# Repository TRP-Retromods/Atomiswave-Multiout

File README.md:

# Atomiswave Multiout
---
Get Composite, RGB or S-Video output from your Atomiswave, using the VGA output

(c) 2023 by The Real Phoenix
Design from Mike Chi's VGA2SCART

---

## Features:
- The motherboard is doing all the job, the "hat" or daughterboard is the one with the output connectors, so you can make one for your needs
- PAL/NTSC selection
- LP Filter
- Audio Line-in level is driven from the daughterboard, leaving the ability to keep pass-trought audio for amp already present inside a cabinet

## Notes:
- You'll need to program the CDCE either with using a DFO programmer or ask your ICs provider to do it for you.
- The connector to audio/power is tricky to find, I found some on eBay: https://www.ebay.ca/itm/184681041924

---
### Links for the Programmer and classic DFO:
https://nfggames.com/forum2/index.php?topic=5744.0
https://oshpark.com/profiles/micro

https://circuit-board.de/forum/index.php/Thread/7810-Sega-32X-Switchless-Mod-f%C3%BCr-Mega-Drive-1-und-auch-2/?s=005d89b5fd35d5ff06d198493b633b89d1ca043f

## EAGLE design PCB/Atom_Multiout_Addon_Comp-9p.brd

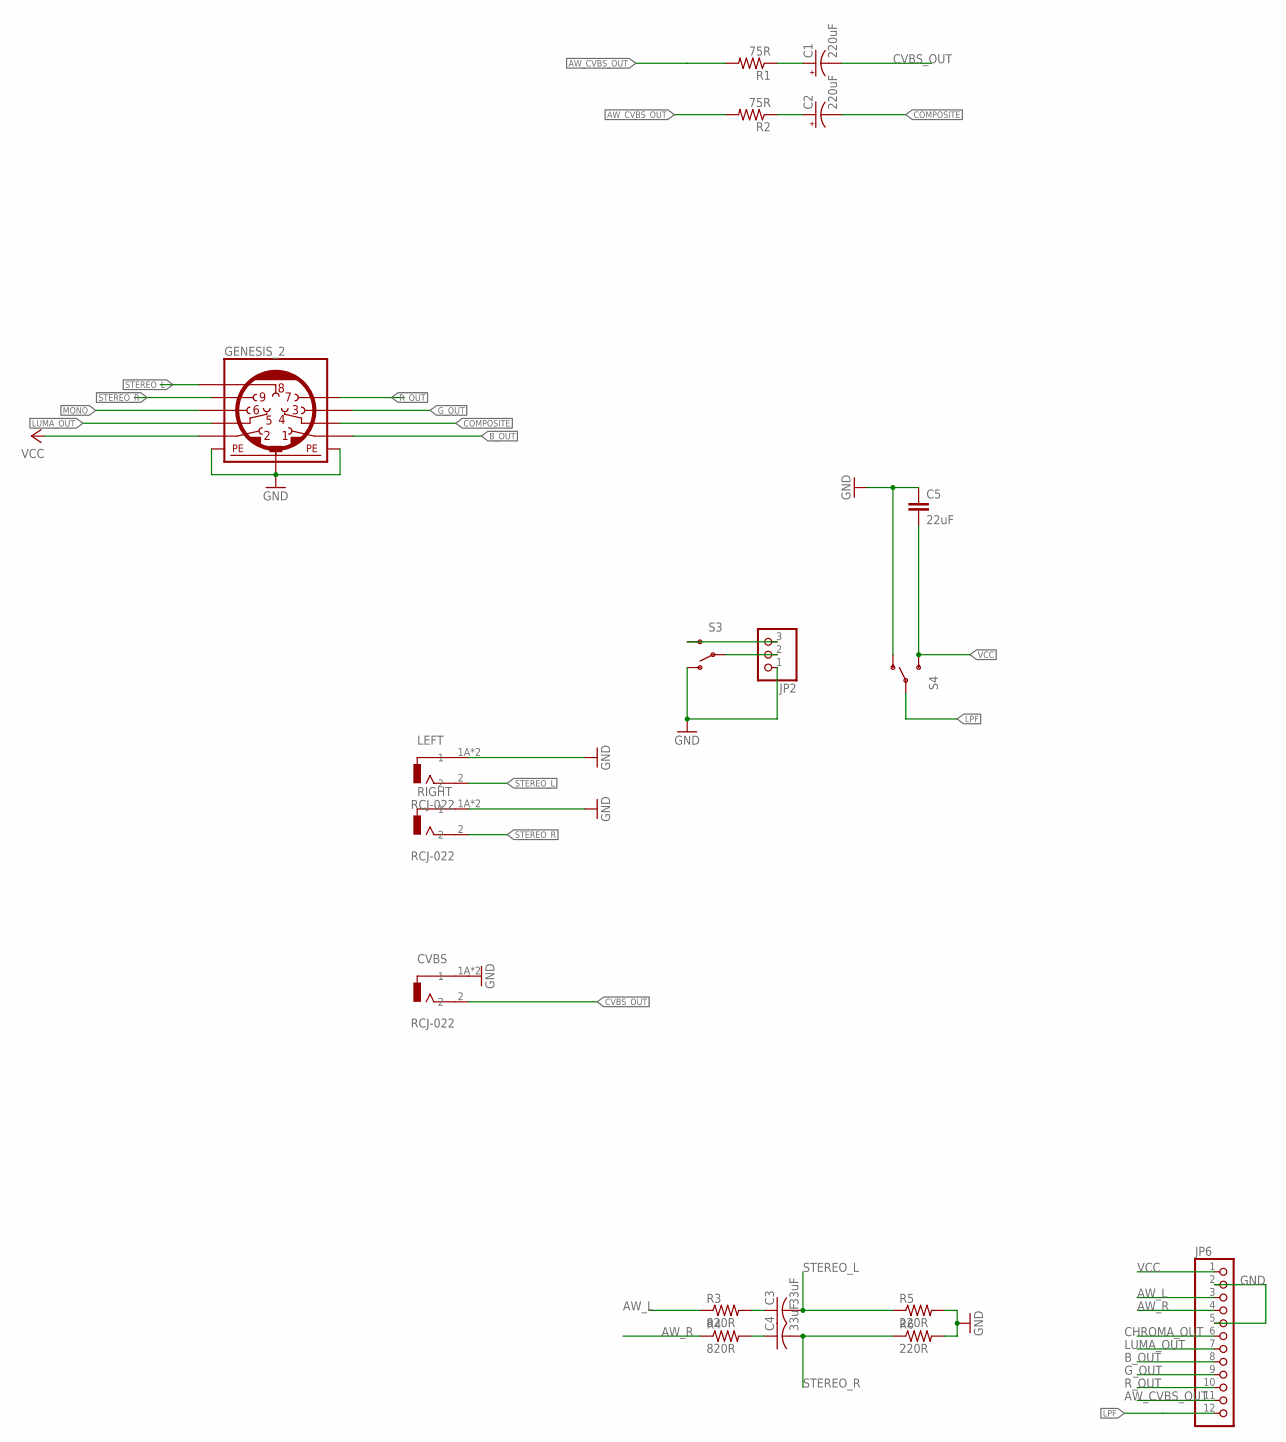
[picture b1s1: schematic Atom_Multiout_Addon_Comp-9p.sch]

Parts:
C1, C2: 220uF; D/7343-31W
C3, C4: 33uF; C1206K
C5: 22uF; C0603
CVBS: RCJ-022; CUI_RCJ-022
GENESIS_2: MINI_DIN_9; M_DIN9
JP2: PINHD-1X03_2.54-S; 1X03-S
JP6: PINHD-1X12_2.54-S; 1X12-S
LEFT: RCJ-022; CUI_RCJ-022
R1, R2: 75R; R1206
R3, R4: 820R; R1206
R5, R6: 220R; R1206
RIGHT: RCJ-022; CUI_RCJ-022
S3, S4: SWITCH-SPDT-SMD-A; SWITCH-SPST-SMD-A

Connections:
AW_CVBS_OUT: JP6.11, R1.2, R2.2
AW_L: JP6.3, R3.1
AW_R: JP6.4, R4.1
B_OUT: GENESIS_2.1, JP6.8
CHROMA_OUT: JP6.6
COMPOSITE: C2.-, GENESIS_2.4
CVBS_OUT: C1.-, CVBS.2
GND: C5.1, CVBS.1A (1), CVBS.1B (1), GENESIS_2.SH1 (PE1), GENESIS_2.SH2 (PE2), GENESIS_2.SH3 (PE3), JP2.1, JP6.2, JP6.5, LEFT.1A (1), LEFT.1B (1), R5.2, R6.2, RIGHT.1A (1), RIGHT.1B (1), S3.1 (O), S4.1 (O)
G_OUT: GENESIS_2.3, JP6.9
LPF: JP6.12, S4.2
LUMA_OUT: GENESIS_2.5, JP6.7
MONO: GENESIS_2.6
unnamed: C2.+, R2.1
unnamed: JP2.3, S3.3 (S)
unnamed: C1.+, R1.1
unnamed: C4.1, R4.2
unnamed: C3.1, R3.2
unnamed: JP2.2, S3.2
R_OUT: GENESIS_2.7, JP6.10
STEREO_L: C3.2, GENESIS_2.8, LEFT.2, R5.1
STEREO_R: C4.2, GENESIS_2.9, R6.1, RIGHT.2
VCC: C5.2, GENESIS_2.2, JP6.1, S4.3 (S)

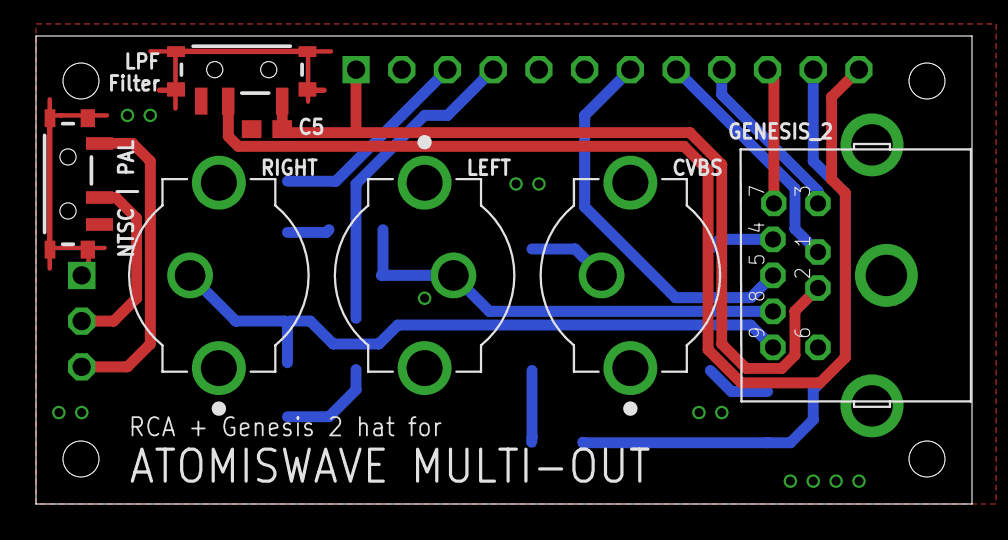
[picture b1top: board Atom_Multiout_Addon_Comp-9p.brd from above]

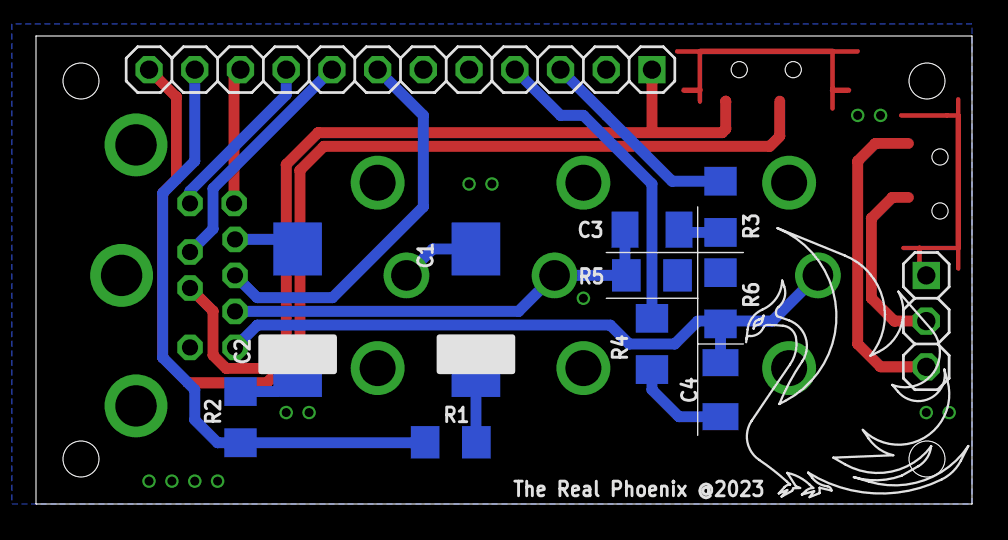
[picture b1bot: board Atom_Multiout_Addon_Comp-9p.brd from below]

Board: 2 copper layers, 52.0 x 26.0 mm, 20 parts (13 on the bottom side), 20 nets.

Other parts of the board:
U$1: LOGO

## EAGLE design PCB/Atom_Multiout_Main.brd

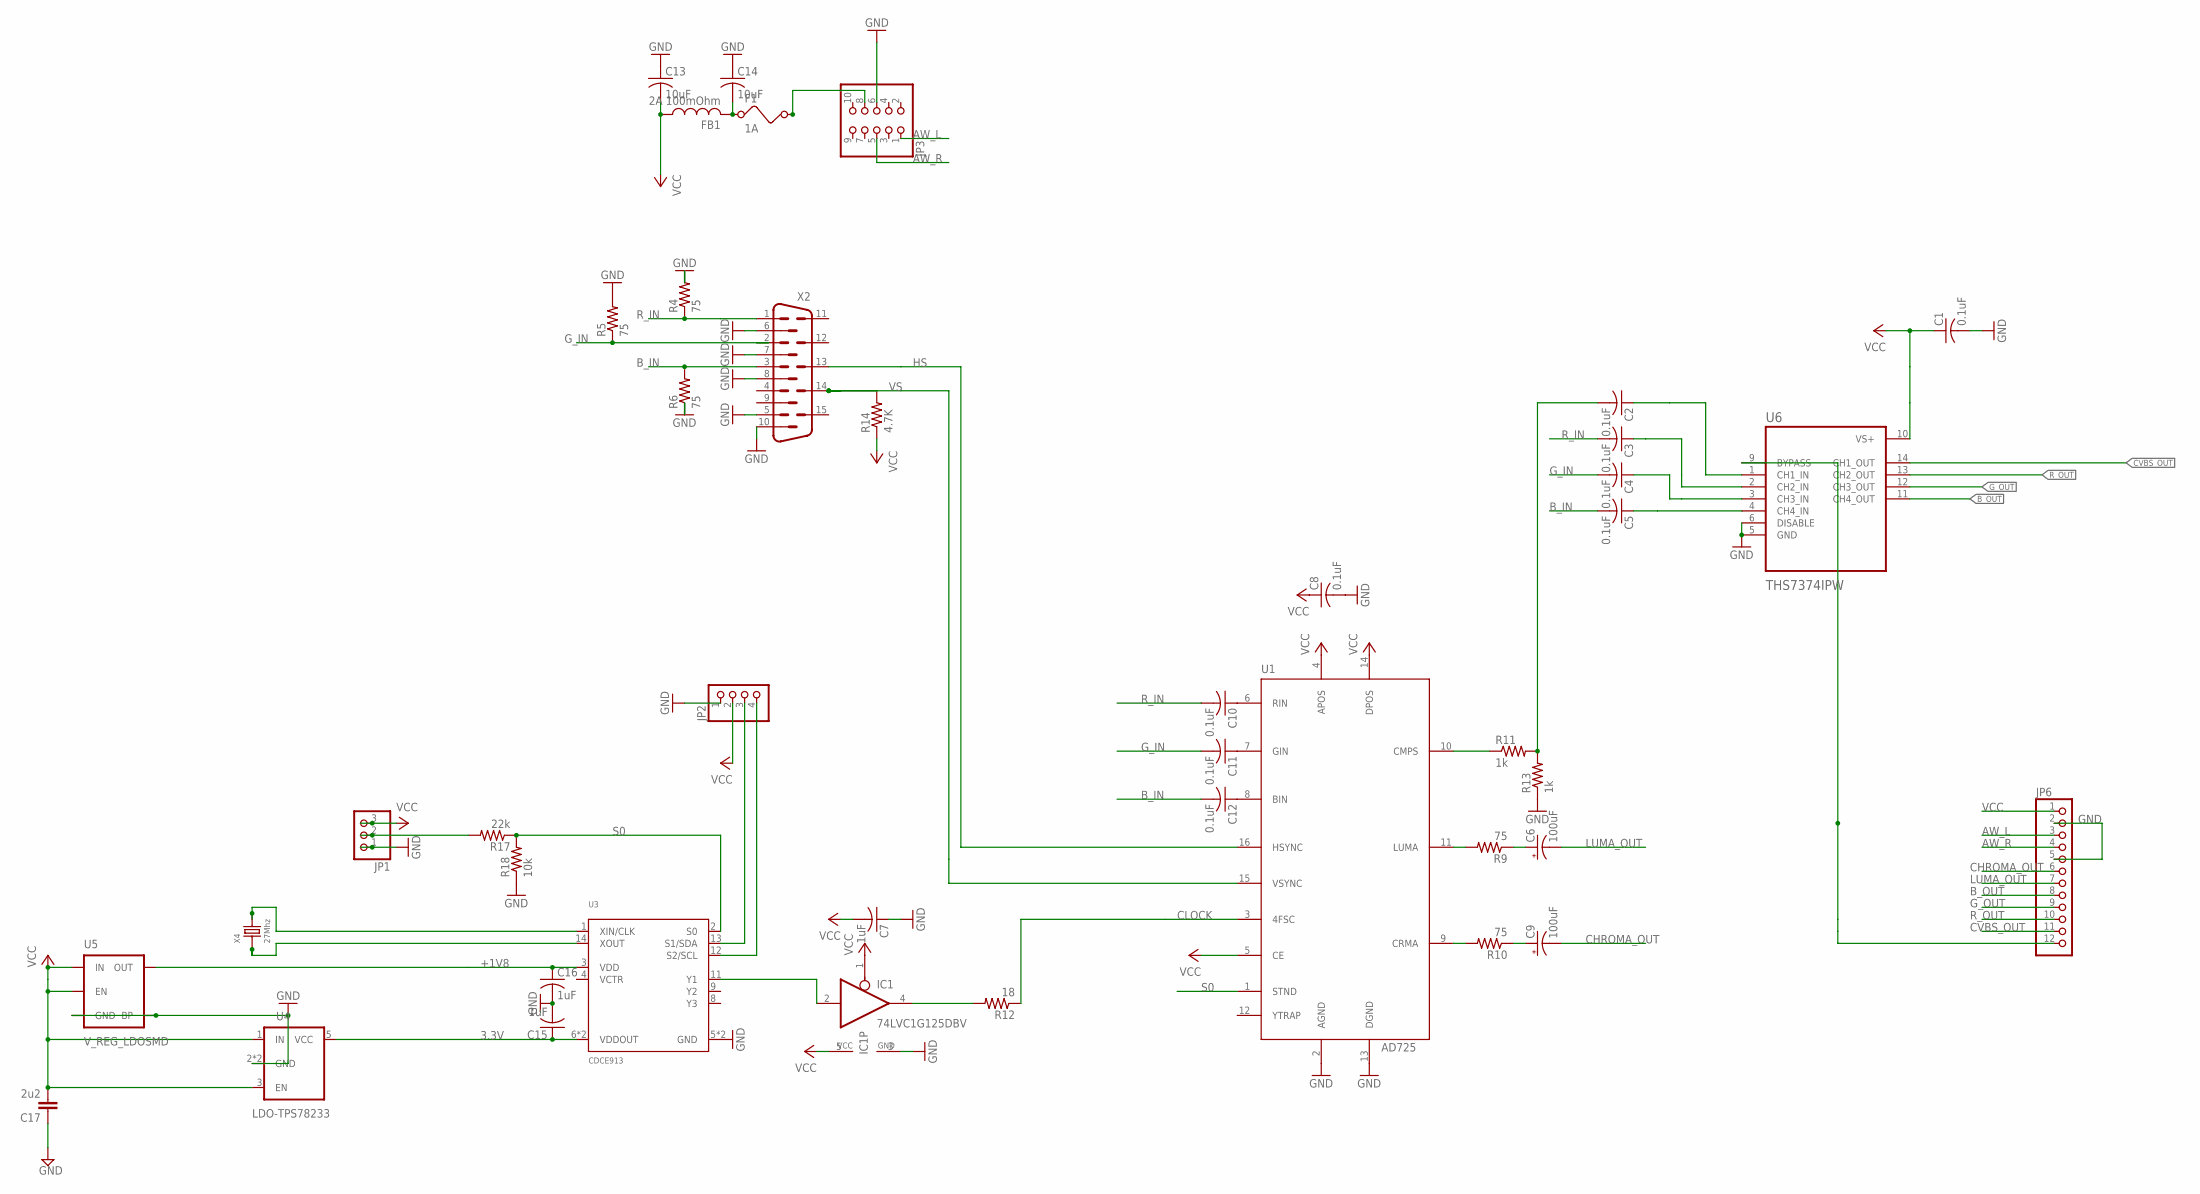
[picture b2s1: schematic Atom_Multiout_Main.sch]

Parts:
C1, C2, C3, C4, C5, C8, C10, C11, C12: 0.1uF; C0603@1
C6, C9: 100uF; C/6032-28R
C7, C15, C16: 1uF; C0603@1
C13, C14: 10uF; C0603@1
C17: 2u2; C0603
F1: 1A; 1812
FB1: 2A 100mOhm; 0805
IC1: 74LVC1G125DBV; SOT23-5
JP1: PINHD-1X03_2.54-S; 1X03-S
JP2: PINHD-1X04_2.00; 1X04M
JP3: PINHD-2X05_2.00; 2X05M
JP6: PINHD-1X12_2.54-S; 1X12-S
R4, R5, R6, R9, R10: 75; R0603
R11, R13: 1k; R0603
R12: 18; R0603
R14: 4.7K; R0603
R17: 22k; R0603
R18: 10k; R0603
U1: AD725; SOIC16W
U3: CDCE913; TSSOP14
U4: LDO-TPS78233; SOT23-5
U5: V_REG_LDOSMD; SOT23-5
U6: THS7374IPW; SOP65P640X120-14N
X2: HM15V; HDM15V
X4: 27Mhz; X2-SMD-5.0X3.2X1.3MM

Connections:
3.3V: C15.1, U3.6 (VDDOUT), U3.7 (VDDOUT), U4.5 (VCC)
+1V8: C16.1, U3.3 (VDD), U5.5 (OUT)
AW_L: JP3.1, JP6.3
AW_R: JP3.5, JP6.4
B_IN: C5.2, C12.2, R6.2, X2.3
B_OUT: JP6.8, U6.11 (CH4_OUT)
CHROMA_OUT: C9.-, JP6.6
CLOCK: R12.1, U1.3 (4FSC)
CVBS_OUT: JP6.11, U6.14 (CH1_OUT)
GND: C1.2, C7.1, C8.2, C13.1, C14.1, C15.2, C16.2, C17.1, IC1.3 (GND), JP1.1, JP2.1, JP3.6, JP6.2, JP6.5, R4.2, R5.2, R6.1, R13.1, R18.1, U1.2 (AGND), U1.13 (DGND), U3.5 (GND), U3.10 (GND), U4.2 (GND), U4.4 (GND), U5.2 (GND), U5.4 (BP), U6.5 (GND), U6.6 (DISABLE), X2.5, X2.6, X2.7, X2.8, X2.10
G_IN: C4.2, C11.2, R5.1, X2.2
G_OUT: JP6.9, U6.12 (CH3_OUT)
HS: U1.16 (HSYNC), X2.13
LPF: JP6.12, U6.9 (BYPASS)
LUMA_OUT: C6.-, JP6.7
unnamed: C2.1, U6.1 (CH1_IN)
unnamed: IC1.4 (O), R12.2
unnamed: C4.1, U6.3 (CH3_IN)
unnamed: C3.1, U6.2 (CH2_IN)
unnamed: C5.1, U6.4 (CH4_IN)
unnamed: C2.2, R11.2, R13.2
unnamed: R11.1, U1.10 (CMPS)
unnamed: C10.1, U1.6 (RIN)
unnamed: C11.1, U1.7 (GIN)
unnamed: C12.1, U1.8 (BIN)
unnamed: R9.2, U1.11 (LUMA)
unnamed: R10.2, U1.9 (CRMA)
unnamed: C6.+, R9.1
unnamed: C9.+, R10.1
unnamed: F1.2, JP3.8
unnamed: C14.2, F1.1, FB1.2
unnamed: IC1.2 (I), U3.11 (Y1)
unnamed: JP1.2, R17.2
unnamed: U3.1 (XIN/CLK), X4.2
unnamed: U3.14 (XOUT), X4.1
unnamed: JP2.3, U3.13 (S1/SDA)
unnamed: JP2.4, U3.12 (S2/SCL)
R_IN: C3.2, C10.2, R4.1, X2.1
R_OUT: JP6.10, U6.13 (CH2_OUT)
S0: R17.1, R18.2, U1.1 (STND), U3.2 (S0)
VCC: C1.1, C7.2, C8.1, C13.2, C17.2, FB1.1, IC1.1 (OE), IC1.5 (VCC), JP1.3, JP2.2, JP6.1, R14.1, U1.4 (APOS), U1.5 (CE), U1.14 (DPOS), U4.1 (IN), U4.3 (EN), U5.1 (IN), U5.3 (EN), U6.10 (VS+)
VS: R14.2, U1.15 (VSYNC), X2.14

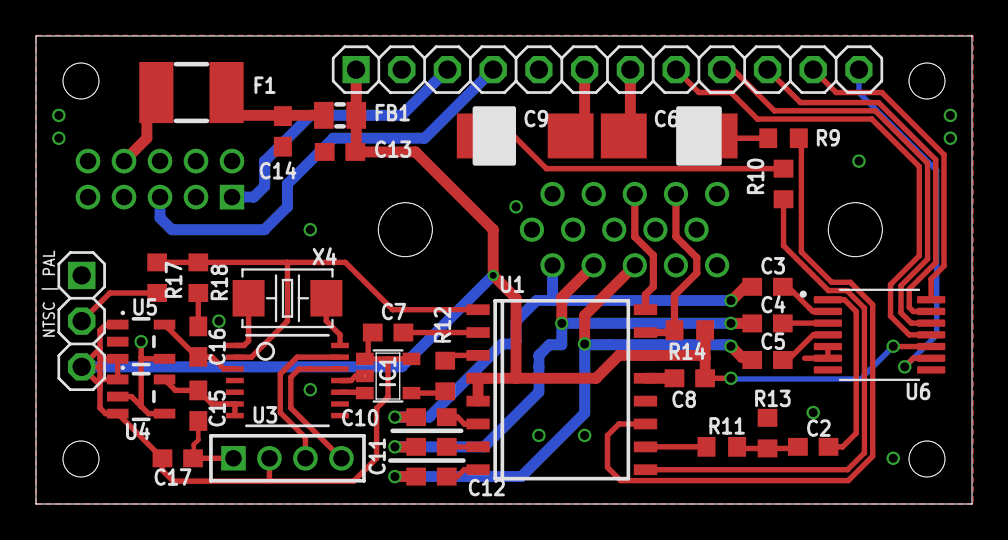
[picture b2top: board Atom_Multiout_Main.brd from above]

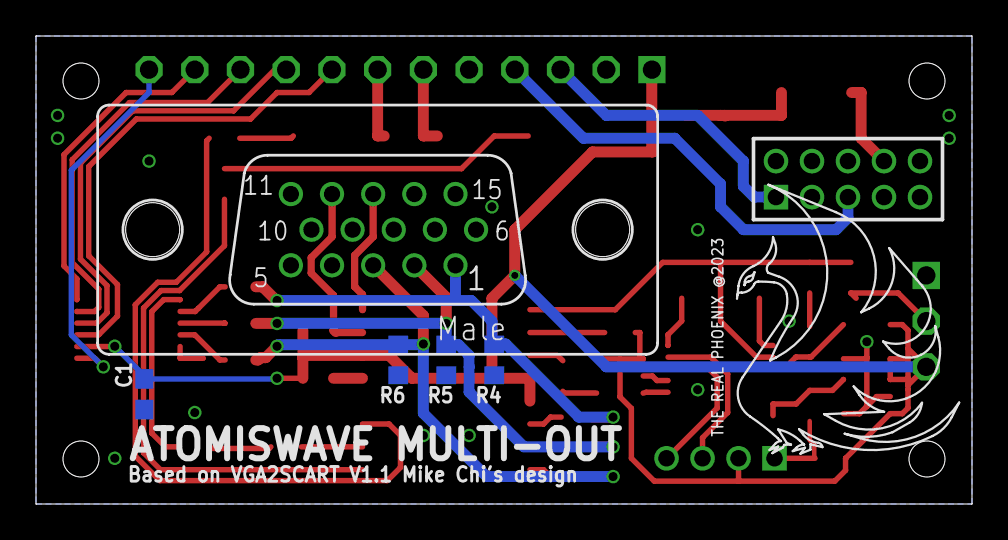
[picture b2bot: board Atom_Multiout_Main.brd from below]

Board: 2 copper layers, 52.0 x 26.0 mm, 43 parts (7 on the bottom side), 42 nets.

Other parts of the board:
U$1: LOGO

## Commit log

2023-05-23 Create Atomiswave-Multiout
    Create Atomiswave-Multiout

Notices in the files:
parts and their libraries:
SparkFun-Electromechanical: Licensing: Creative Commons ShareAlike 4.0 International - https://creativecommons.org/licenses/by-sa/4.0
m-pad-2.1: License : GNU General Public License version 2 (see bottom)
